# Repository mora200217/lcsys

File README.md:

# lcsys
Sensor de nivel capacitivo. Practica 2 Sensores y actuadores

## Elemento primario de medida
=======

# Spice sim 

Aquí se encuentran las simulacion en LTspice de los subcircuitos solicitados. Sientanse libres de modificar los parámetros para probar sus diseños y comparar con los valores experimentales 

### Circuito oscilador de Wien 
Es un puente Resito-capacitivo que genera una onda senoidal como señal de salida. Permite se usado como fuente alterna a baja tensión, o como un modulador de frecuencia. 

$$
    f_0 = \frac{1}{2\pi RC}
$$

Con las siguientes recomendaciones de estabilidad 

$$
    \frac{Ra}{Rb} \approx 2 \hspace{20pt} R \gt 1~\text{k}\Omega 
$$

### LM331 
Circuito integrado (IC) conversor de tensión-frecuencia y viscecersa. Nos permitirá extraer la modulación de frecuencia fruto del cambio de capacitancia del sensor, a una señal de tensión que podamos digitalizar. Buscamos que la respuesta sea lo más lineal posible.

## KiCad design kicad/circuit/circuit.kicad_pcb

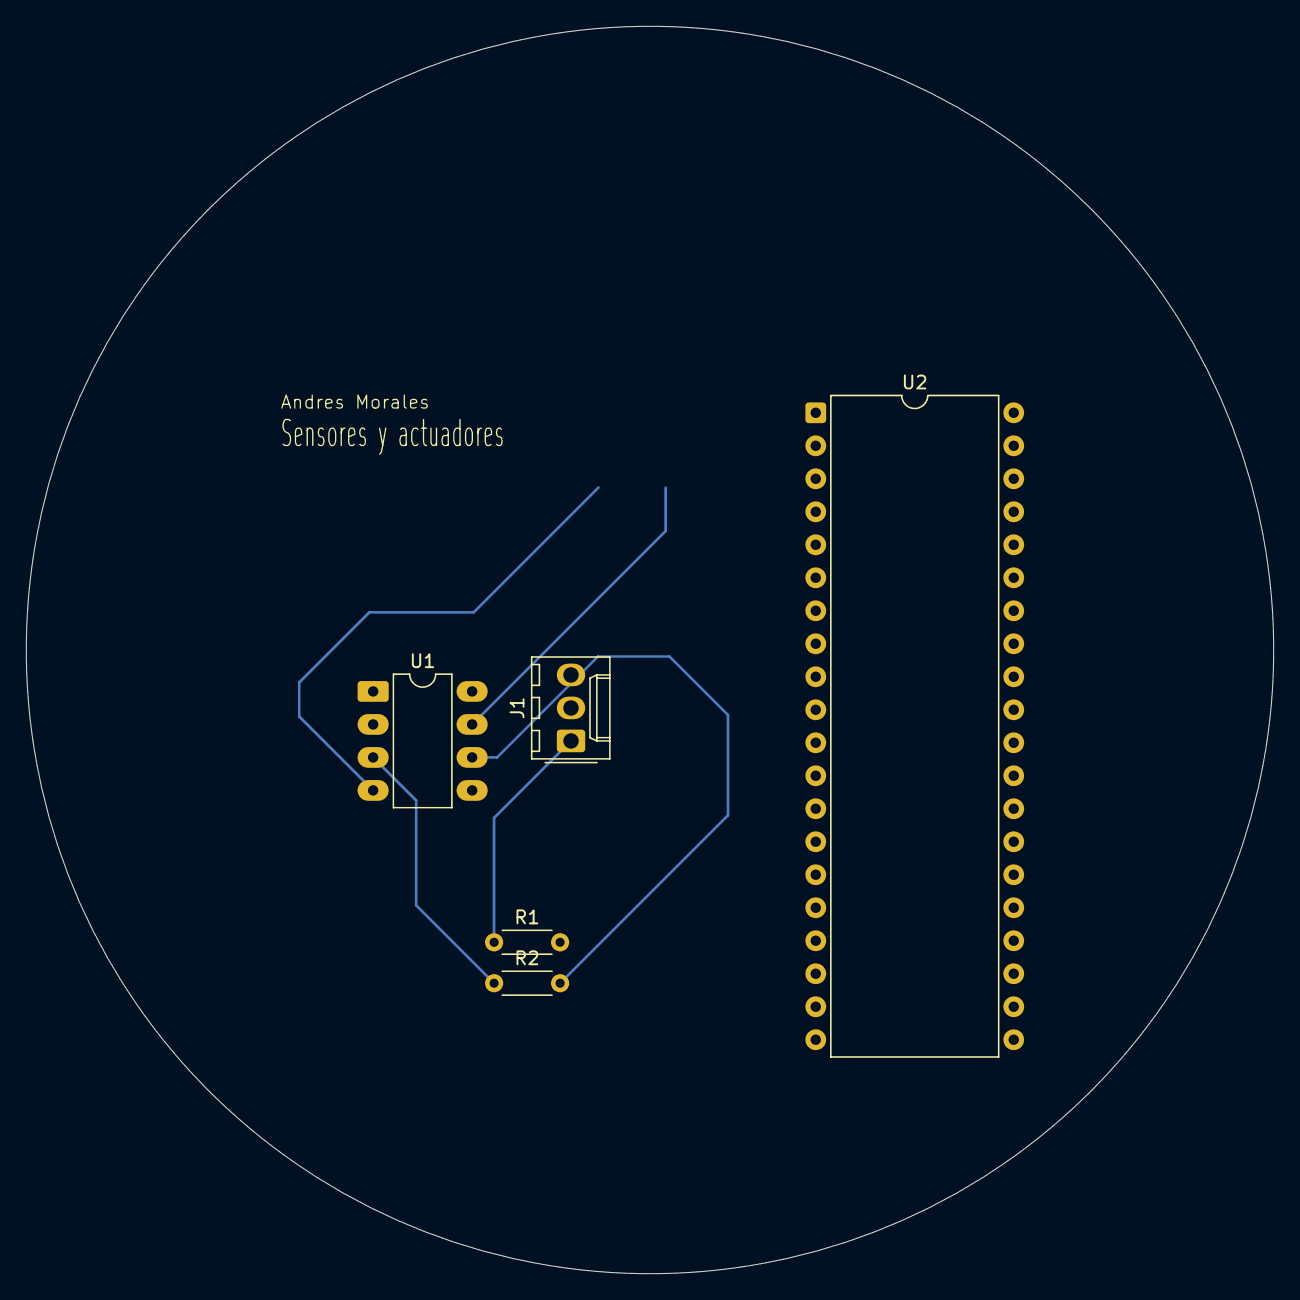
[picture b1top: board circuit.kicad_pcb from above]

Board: 2 copper layers, 96.0 x 96.0 mm, 5 parts (0 on the bottom side), 3 nets.

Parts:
J1: Conn_01x03_Pin; Molex_KK-254_AE-6410-03A_1x03_P2.54mm_Vertical
R1, R2: R; R_Axial_DIN0204_L3.6mm_D1.6mm_P5.08mm_Horizontal
U1: LM741; DIP-8_W7.62mm_LongPads
U2: PIC18F4550-IP; DIP-40_W15.24mm

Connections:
unnamed: J1.1, R1.1
unnamed: R2.2, U1.6
unnamed: R1.2, R2.1, U1.3 (+)

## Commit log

2025-05-25 [Add] Wien bridge
2025-05-25 [New] READMe for LTspice sim.
2025-05-25 [New] README for sim and wien_bridge circuit
2025-05-25 [update]
2025-05-29 [Update] Puente de Wien. Sim en matlab
2025-05-30 [Update] coreccion para versiones anteriores
